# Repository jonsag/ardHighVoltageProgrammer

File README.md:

# ardHighVoltageProgrammer

## Links

[https://mightyohm.com/blog/products/hv-rescue-shield-2-x/](https://mightyohm.com/blog/products/hv-rescue-shield-2-x/)  

[https://www.instructables.com/HV-Rescue-Simple/](https://www.instructables.com/HV-Rescue-Simple/)  
[https://mightyohm.com/blog/2008/09/arduino-based-avr-high-voltage-programmer/](https://mightyohm.com/blog/2008/09/arduino-based-avr-high-voltage-programmer/)  
[https://microtherion.github.io/ScratchMonkey/HVPP.html](https://microtherion.github.io/ScratchMonkey/HVPP.html)  
[https://www.instructables.com/AVR-High-voltage-programming-Fuses-rescue/](https://www.instructables.com/AVR-High-voltage-programming-Fuses-rescue/)  
[http://denki.world3.net/avr_rescue.html](http://denki.world3.net/avr_rescue.html)  

[https://www.gmsystems.com/switching-reg-calculator-for-mc-34063-or-mc33063.html](https://www.gmsystems.com/switching-reg-calculator-for-mc-34063-or-mc33063.html)

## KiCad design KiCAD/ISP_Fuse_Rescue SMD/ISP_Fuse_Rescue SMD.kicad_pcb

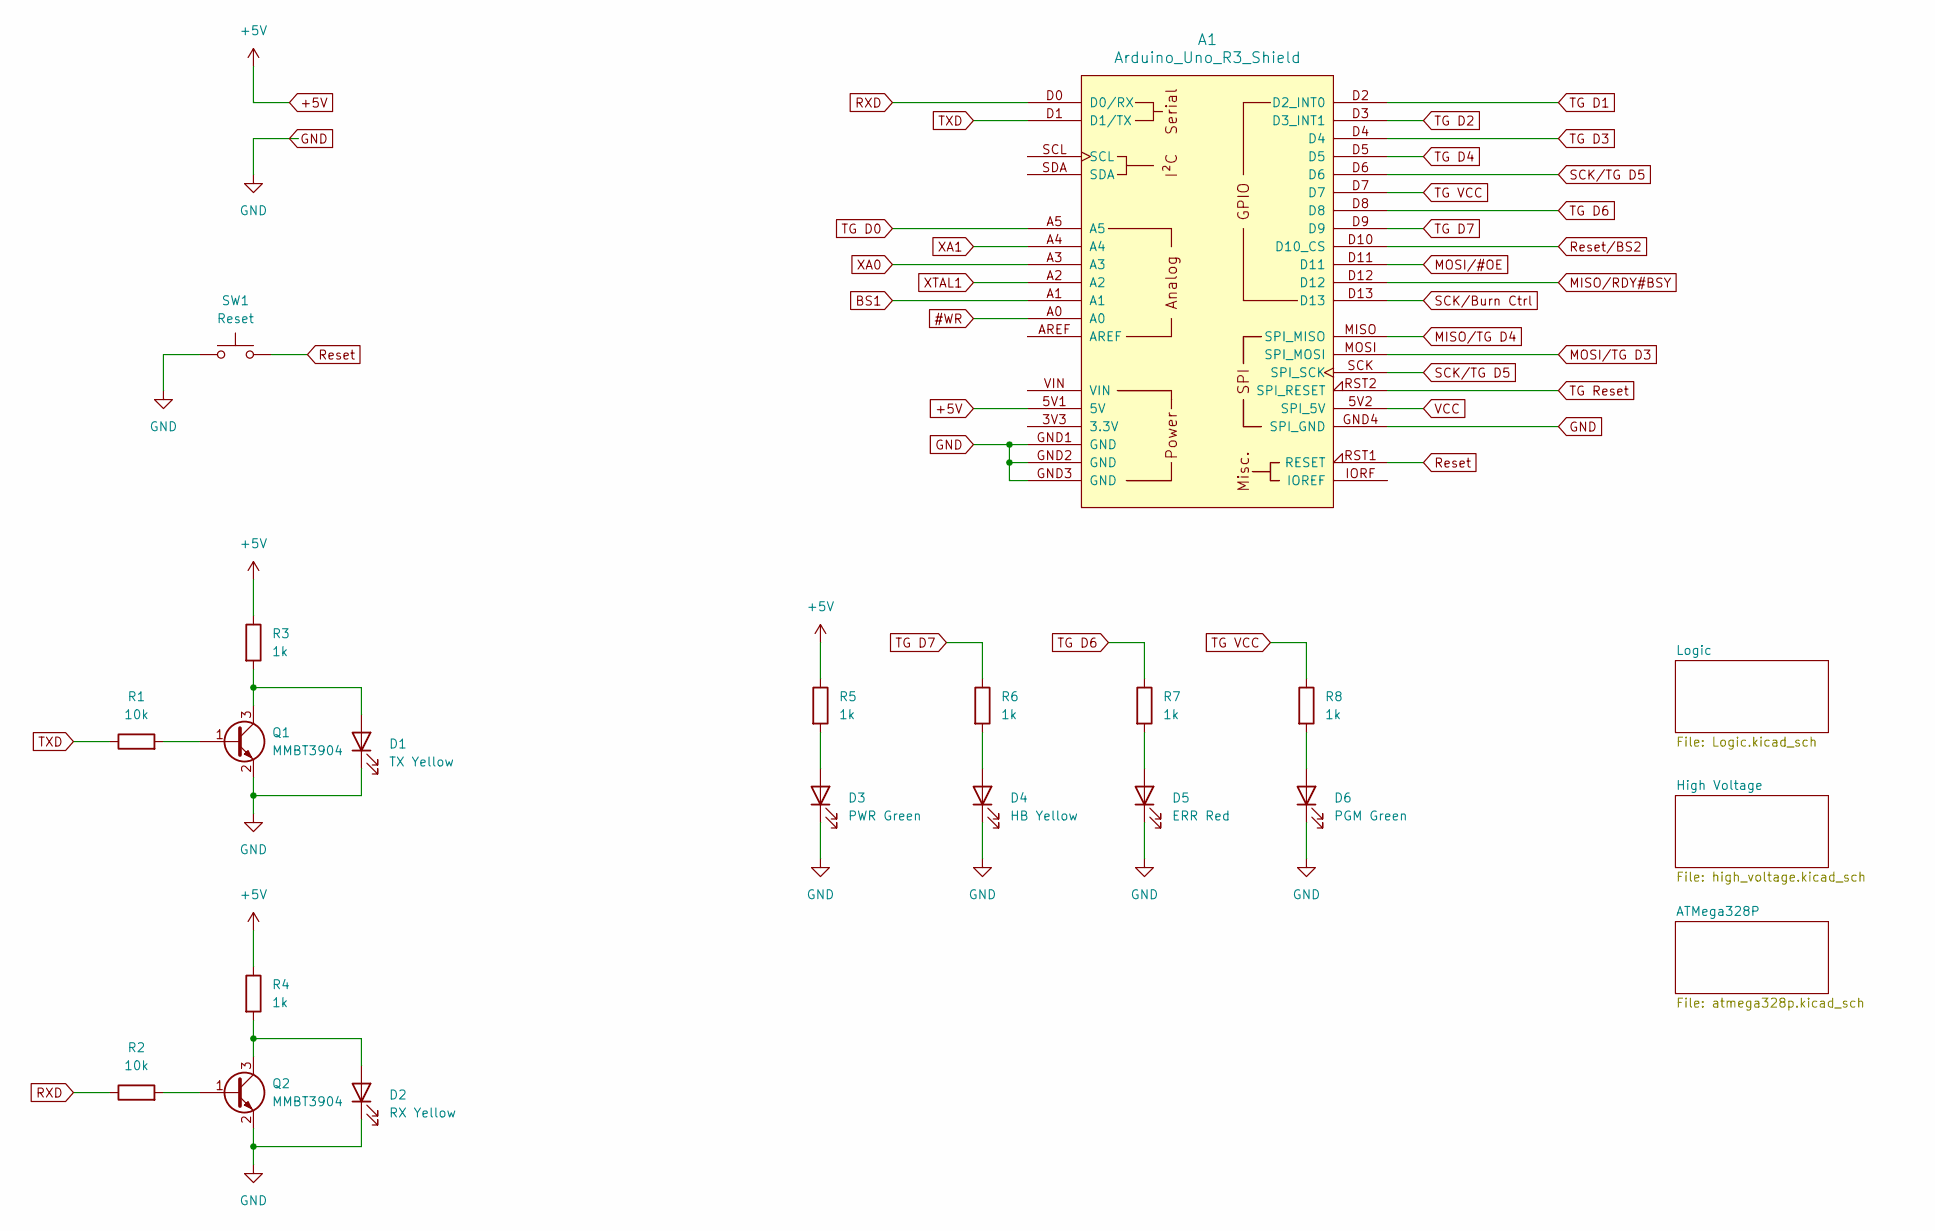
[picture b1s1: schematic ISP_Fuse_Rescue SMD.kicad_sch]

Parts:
A1: Arduino_Uno_R3_Shield; Arduino_UNO_R3_shield_incl ICSP_headers_large
D1: TX Yellow; LED_0805_2012Metric_Pad1.15x1.40mm_HandSolder
D2: RX Yellow; LED_0805_2012Metric_Pad1.15x1.40mm_HandSolder
D3: PWR Green; LED_0805_2012Metric_Pad1.15x1.40mm_HandSolder
D4: HB Yellow; LED_0805_2012Metric_Pad1.15x1.40mm_HandSolder
D5: ERR Red; LED_0805_2012Metric_Pad1.15x1.40mm_HandSolder
D6: PGM Green; LED_0805_2012Metric_Pad1.15x1.40mm_HandSolder
Q1, Q2: MMBT3904; SOT-23_Handsoldering
R1, R2: 10k; R_1206_3216Metric_Pad1.30x1.75mm_HandSolder
R3, R4, R5, R6, R7, R8: 1k; R_1206_3216Metric_Pad1.30x1.75mm_HandSolder
SW1: Reset; Switch tactile Omron B3S SMD

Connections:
#WR: A1.A0; also elsewhere on the board
+5V: A1.5V1 (5V), R3.1, R4.1, R5.1; also elsewhere on the board
BS1: A1.A1; also elsewhere on the board
GND: A1.GND1 (GND), A1.GND2 (GND), A1.GND3 (GND), A1.GND4 (SPI_GND), D1.1 (K), D2.1 (K), D3.1 (K), D4.1 (K), D5.1 (K), D6.1 (K), Q1.2 (E), Q2.2 (E), SW1.1; also elsewhere on the board
MISO/RDY#BSY: A1.D12; also elsewhere on the board
MISO/TG D4: A1.MISO (SPI_MISO); also elsewhere on the board
MOSI/#OE: A1.D11; also elsewhere on the board
MOSI/TG D3: A1.MOSI (SPI_MOSI); also elsewhere on the board
unnamed: D1.2 (A), Q1.3 (C), R3.2
unnamed: D2.2 (A), Q2.3 (C), R4.2
unnamed: D3.2 (A), R5.2
unnamed: D4.2 (A), R6.2
unnamed: D5.2 (A), R7.2
unnamed: D6.2 (A), R8.2
unnamed: Q1.1 (B), R1.2
unnamed: Q2.1 (B), R2.2
RXD: A1.D0 (D0/RX), R2.1
Reset: A1.RST1 (RESET), SW1.2
Reset/BS2: A1.D10 (D10_CS); also elsewhere on the board
SCK/Burn Ctrl: A1.D13; also elsewhere on the board
SCK/TG D5: A1.D6, A1.SCK (SPI_SCK); also elsewhere on the board
TG D0: A1.A5; also elsewhere on the board
TG D1: A1.D2 (D2_INT0); also elsewhere on the board
TG D2: A1.D3 (D3_INT1); also elsewhere on the board
TG D3: A1.D4; also elsewhere on the board
TG D4: A1.D5; also elsewhere on the board
TG D6: A1.D8, R7.1; also elsewhere on the board
TG D7: A1.D9, R6.1; also elsewhere on the board
TG Reset: A1.RST2 (SPI_RESET)
TG VCC: A1.D7, R8.1; also elsewhere on the board
TXD: A1.D1 (D1/TX), R1.1
VCC: A1.5V2 (SPI_5V)
XA1: A1.A4; also elsewhere on the board
XTAL1: A1.A2; also elsewhere on the board

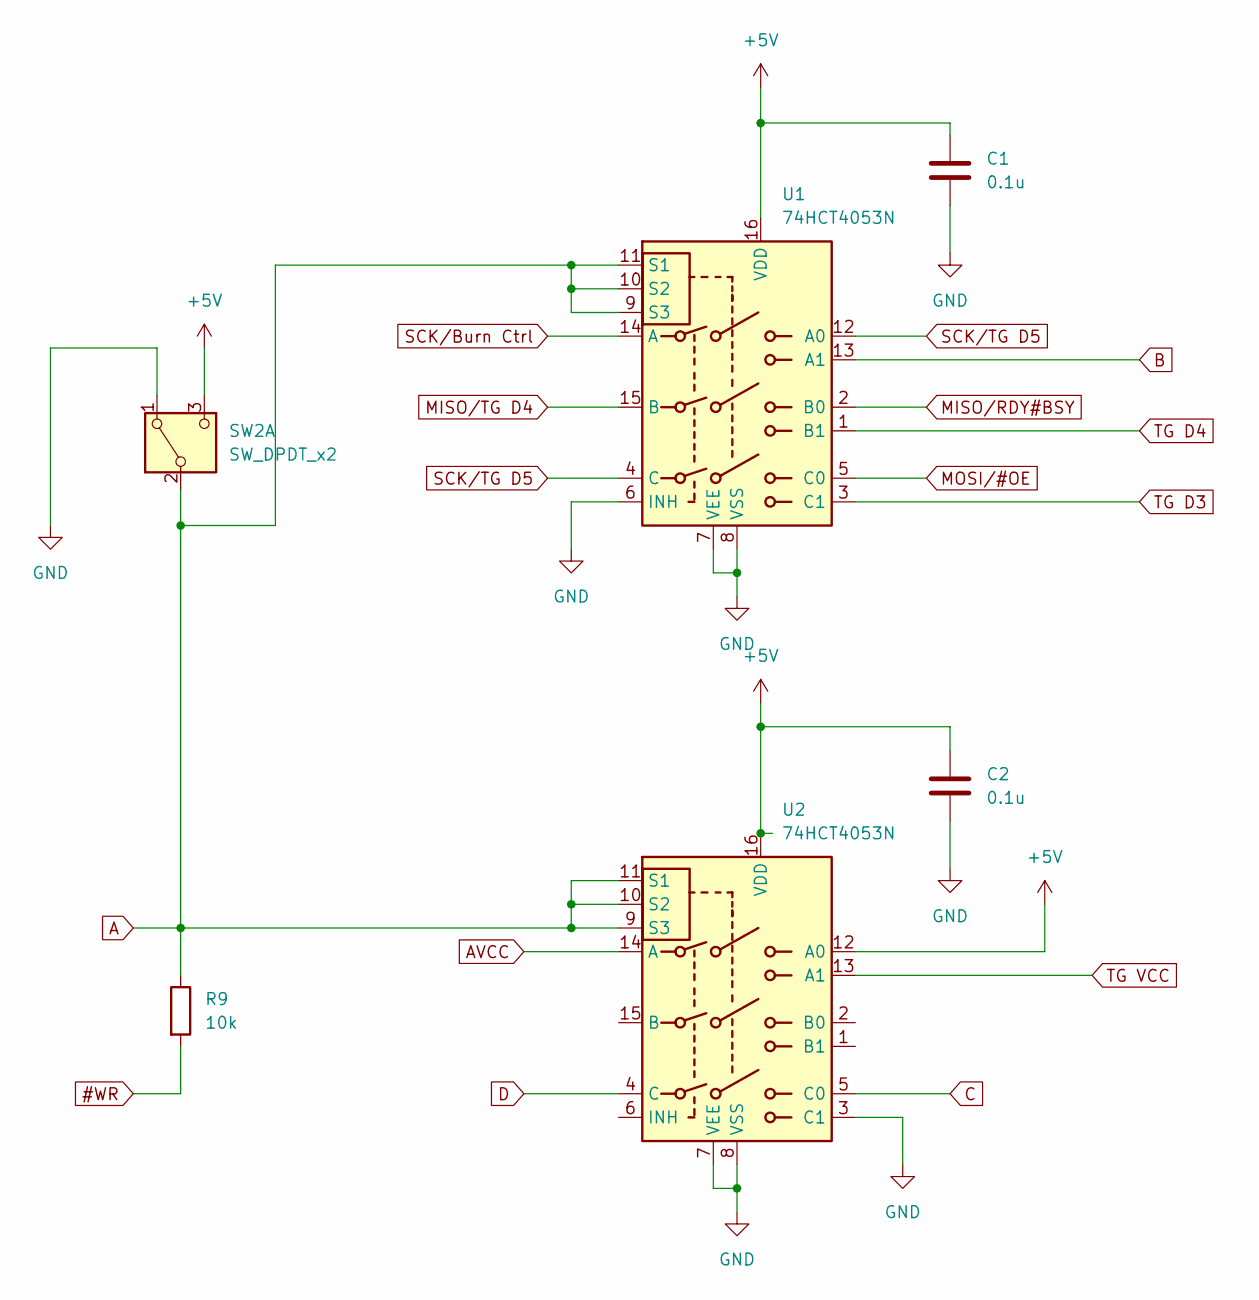
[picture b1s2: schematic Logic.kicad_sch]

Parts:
C1, C2: 0.1u; C_1206_3216Metric_Pad1.33x1.80mm_HandSolder
R9: 10k; R_1206_3216Metric_Pad1.30x1.75mm_HandSolder
SW2: SW_DPDT_x2; Switch slide 2-pole on-on
U1, U2: 74HCT4053N; SOIC-16_3.9x9.9mm_P1.27mm

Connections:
#WR: R9.2; also elsewhere on the board
+5V: C1.1, C2.1, SW2.3 (C), U1.16 (VDD), U2.12 (A0), U2.16 (VDD); also elsewhere on the board
A: R9.1, SW2.2 (B), U1.9 (S3), U1.10 (S2), U1.11 (S1), U2.9 (S3), U2.10 (S2), U2.11 (S1); also elsewhere on the board
AVCC: U2.14 (A); also elsewhere on the board
B: U1.13 (A1); also elsewhere on the board
C: U2.5 (C0); also elsewhere on the board
D: U2.4 (C); also elsewhere on the board
GND: C1.2, C2.2, SW2.1 (A), U1.6 (INH), U1.7 (VEE), U1.8 (VSS), U2.3 (C1), U2.7 (VEE), U2.8 (VSS); also elsewhere on the board
MISO/RDY#BSY: U1.2 (B0); also elsewhere on the board
MISO/TG D4: U1.15 (B); also elsewhere on the board
MOSI/#OE: U1.5 (C0); also elsewhere on the board
SCK/Burn Ctrl: U1.14 (A); also elsewhere on the board
SCK/TG D5: U1.4 (C), U1.12 (A0); also elsewhere on the board
TG D3: U1.3 (C1); also elsewhere on the board
TG D4: U1.1 (B1); also elsewhere on the board
TG VCC: U2.13 (A1); also elsewhere on the board

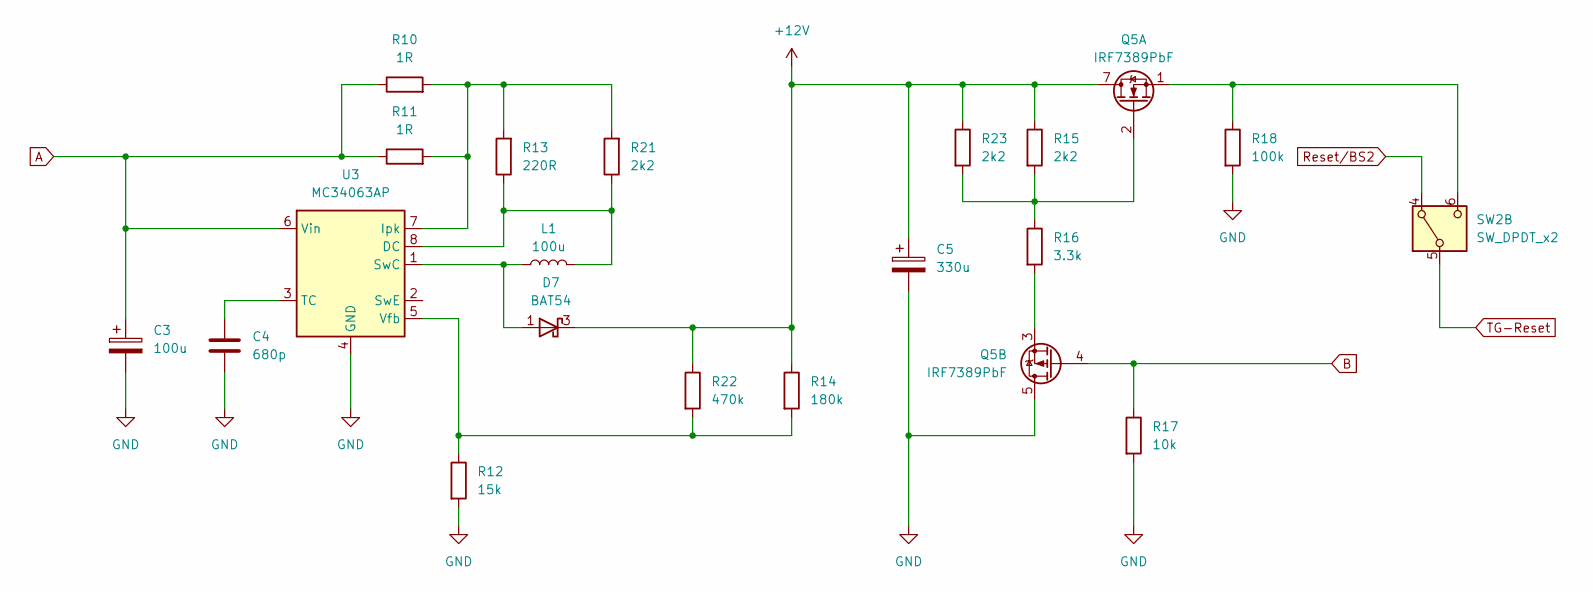
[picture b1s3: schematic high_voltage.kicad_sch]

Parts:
C3: 100u; CP_Elec_8x10
C4: 680p; C_1206_3216Metric_Pad1.33x1.80mm_HandSolder
C5: 330u; CP_Elec_10x10
D7: BAT54; SOT-23_Handsoldering
L1: 100u; L_1210_3225Metric_Pad1.42x2.65mm_HandSolder
Q5: IRF7389PbF; SOIC-8_3.9x4.9mm_P1.27mm
R10, R11: 1R; R_1206_3216Metric_Pad1.30x1.75mm_HandSolder
R12: 15k; R_1206_3216Metric_Pad1.30x1.75mm_HandSolder
R13: 220R; R_1206_3216Metric_Pad1.30x1.75mm_HandSolder
R14: 180k; R_1206_3216Metric_Pad1.30x1.75mm_HandSolder
R15, R21, R23: 2k2; R_1206_3216Metric_Pad1.30x1.75mm_HandSolder
R16: 3.3k; R_1206_3216Metric_Pad1.30x1.75mm_HandSolder
R17: 10k; R_1206_3216Metric_Pad1.30x1.75mm_HandSolder
R18: 100k; R_1206_3216Metric_Pad1.30x1.75mm_HandSolder
R22: 470k; R_1206_3216Metric_Pad1.30x1.75mm_HandSolder
SW2: SW_DPDT_x2; Switch slide 2-pole on-on
U3: MC34063AP; DIP-8_W7.62mm_Socket_w_dip_packet_LongPads

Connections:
+12V: C5.1, D7.3 (K), Q5.7 (D), Q5.8 (D), R14.1, R15.1, R22.1, R23.1
A: C3.1, R10.1, R11.1, U3.6 (Vin); also elsewhere on the board
B: Q5.4 (G), R17.1; also elsewhere on the board
GND: C3.2, C4.2, C5.2, Q5.5 (D), Q5.6 (D), R12.2, R17.2, R18.2, U3.4 (GND); also elsewhere on the board
unnamed: D7.1 (A), L1.1, U3.1 (SwC)
unnamed: Q5.2 (G), R15.2, R16.1, R23.2
unnamed: Q5.1 (S), R18.1, SW2.6 (C)
unnamed: Q5.3 (1), R16.2
unnamed: L1.2, R13.1, R21.1, U3.8 (DC)
unnamed: R10.2, R11.2, R13.2, R21.2, U3.7 (Ipk)
unnamed: C4.1, U3.3 (TC)
unnamed: R12.1, R14.2, R22.2, U3.5 (Vfb)
Reset/BS2: SW2.4 (A); also elsewhere on the board
TG-Reset: SW2.5 (B); also elsewhere on the board

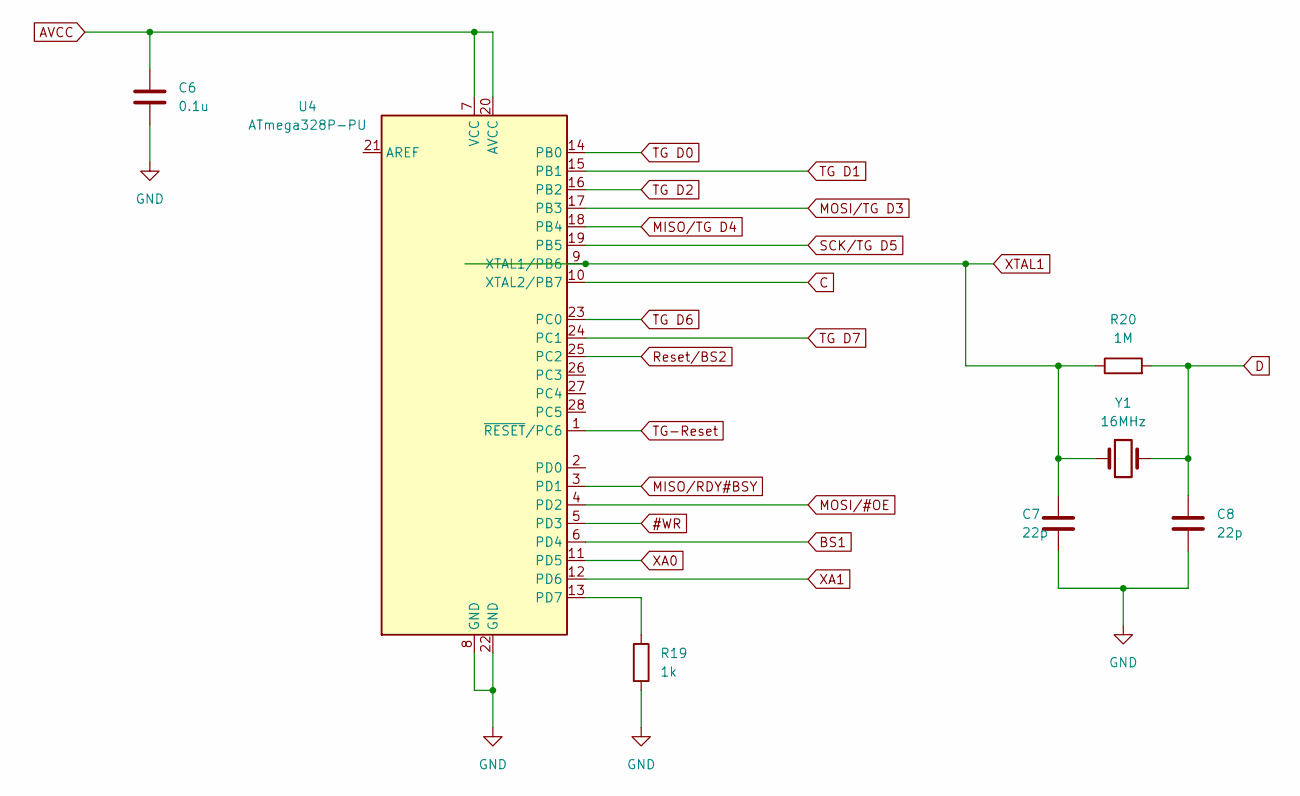
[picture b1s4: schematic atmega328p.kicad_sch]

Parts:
C6: 0.1u; C_1206_3216Metric_Pad1.33x1.80mm_HandSolder
C7, C8: 22p; C_1206_3216Metric_Pad1.33x1.80mm_HandSolder
R19: 1k; R_1206_3216Metric_Pad1.30x1.75mm_HandSolder
R20: 1M; R_1206_3216Metric_Pad1.30x1.75mm_HandSolder
U4: ATmega328P-PU; ZIF_DIP_Socket-28_W6.9_W7.62_W7.62_W12.7_W13.5_large
Y1: 16MHz; Crystal_HC49-4H_Vertical_large

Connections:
#WR: U4.5 (PD3); also elsewhere on the board
AVCC: C6.1, U4.7 (VCC), U4.20 (AVCC); also elsewhere on the board
BS1: U4.6 (PD4); also elsewhere on the board
C: U4.10 (XTAL2/PB7); also elsewhere on the board
D: C8.1, R20.2, Y1.2; also elsewhere on the board
GND: C6.2, C7.2, C8.2, R19.2, U4.8 (GND), U4.22 (GND); also elsewhere on the board
MISO/RDY#BSY: U4.3 (PD1); also elsewhere on the board
MISO/TG D4: U4.18 (PB4); also elsewhere on the board
MOSI/#OE: U4.4 (PD2); also elsewhere on the board
MOSI/TG D3: U4.17 (PB3); also elsewhere on the board
unnamed: R19.1, U4.13 (PD7)
Reset/BS2: U4.25 (PC2); also elsewhere on the board
SCK/TG D5: U4.19 (PB5); also elsewhere on the board
TG D0: U4.14 (PB0); also elsewhere on the board
TG D1: U4.15 (PB1); also elsewhere on the board
TG D2: U4.16 (PB2); also elsewhere on the board
TG D6: U4.23 (PC0); also elsewhere on the board
TG D7: U4.24 (PC1); also elsewhere on the board
TG-Reset: U4.1 (~RESET/PC6); also elsewhere on the board
XA0: U4.11 (PD5)
XA1: U4.12 (PD6); also elsewhere on the board
XTAL1: C7.1, R20.1, U4.9 (XTAL1/PB6), Y1.1; also elsewhere on the board

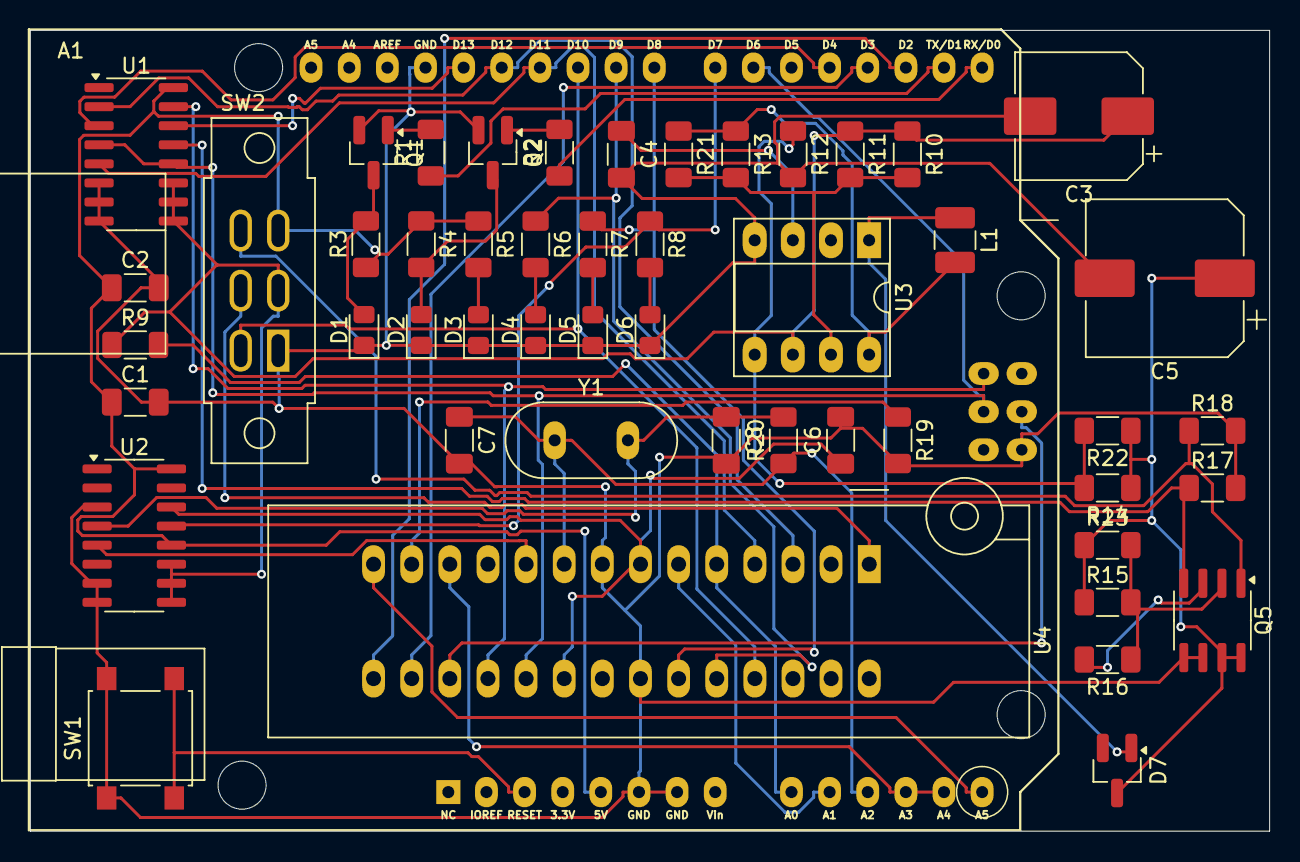
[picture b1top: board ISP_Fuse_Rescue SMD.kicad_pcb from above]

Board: 2 copper layers, 82.6 x 53.3 mm, 50 parts (0 on the bottom side), 48 nets.

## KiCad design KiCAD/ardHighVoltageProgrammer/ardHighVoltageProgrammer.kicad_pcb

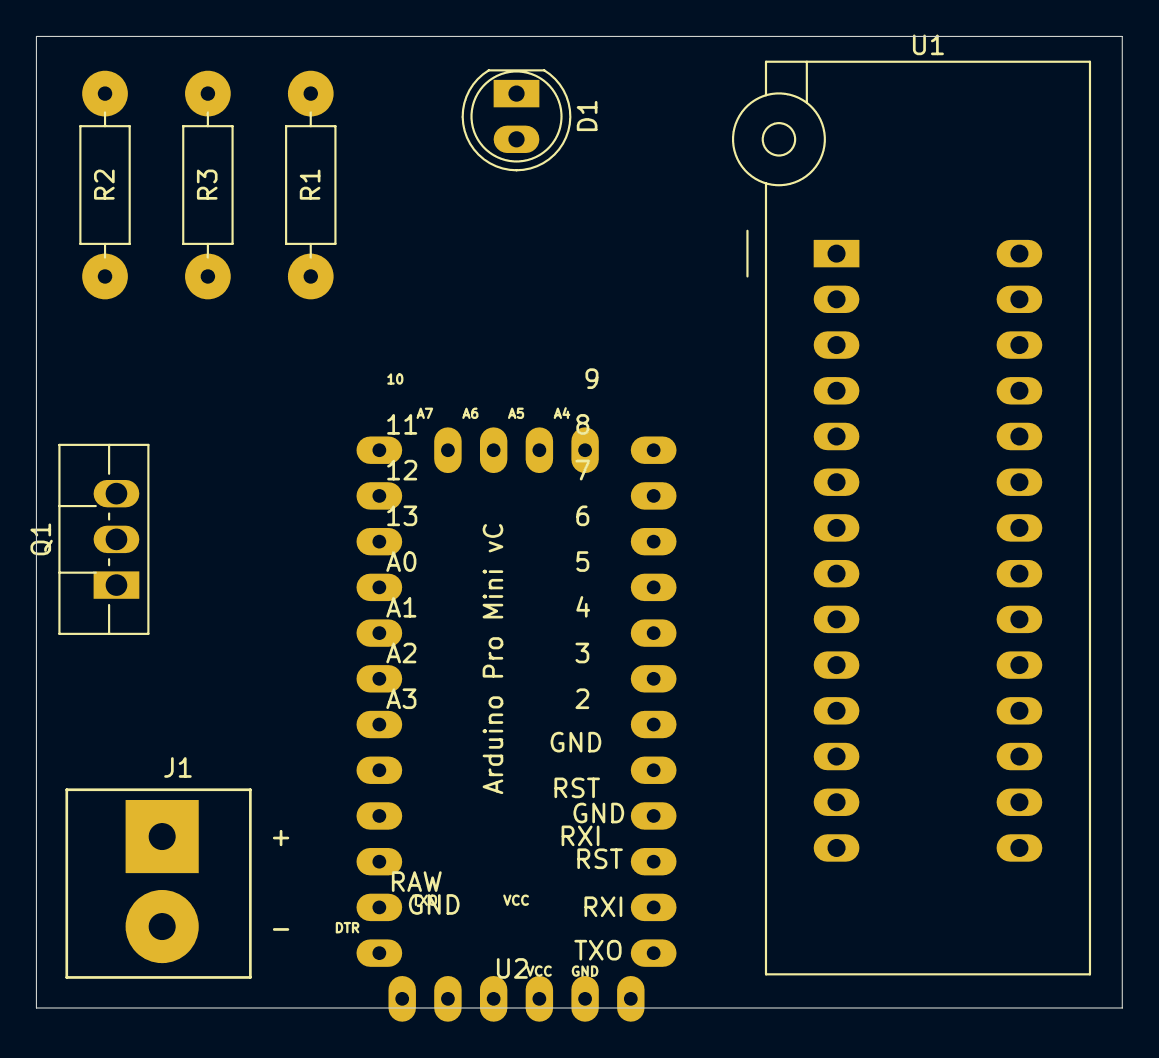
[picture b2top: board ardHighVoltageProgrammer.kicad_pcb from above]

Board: 2 copper layers, 60.3 x 54.0 mm, 8 parts (0 on the bottom side), 24 nets, no tracks yet.

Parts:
D1: LED; LED_D5.0mm_larger_pads
J1: 2-pin_power_input_header; 2-pole_power_in_screw_terminal
Q1: 2N3904; TO-220F-3_Vertical_large
R1: 390R; R_Axial_DIN0207_L6.3mm_D2.5mm_P10.16mm_Horizontal_larger_pa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
R2, R3: 1k; R_Axial_DIN0207_L6.3mm_D2.5mm_P10.16mm_Horizontal_larger_pa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
U1: ATmega328P-PU; ZIF_DIP_Socket-28_W6.9_W7.62_W10.16_W12.7_W13.5_3M_228-4817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
U2: Arduino_Mini_Pro; Arduino_Pro_Mini_vC_larger_pads

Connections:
+5V: D1.2, U1.7, U1.20, U2.16
+12V: J1.1, R2.1
BS1: U1.6, U2.18
BS2: U1.25, U2.12
DATA0: U1.14, U2.19
DATA1: U1.15, U2.1
DATA2: U1.16, U2.5
DATA3: U1.17, U2.6
DATA4: U1.18, U2.7
DATA5: U1.19, U2.8
DATA6: U1.23, U2.9
DATA7: U1.24, U2.10
GND: J1.2, Q1.1, U1.8, U1.22, U2.14
unnamed: D1.1, R1.1
unnamed: Q1.2, R3.2
PAGEL: U1.13, U2.26
RDY: U1.3, U2.21
XA0: U1.11, U2.11
XA1: U1.12, U2.25
XTAL1: U1.9, U2.17
~OE: U1.4, U2.23
~RESET: Q1.3, R2.2, U1.1
~RST: R1.2, R3.1, U2.20
~WR: U1.5, U2.24

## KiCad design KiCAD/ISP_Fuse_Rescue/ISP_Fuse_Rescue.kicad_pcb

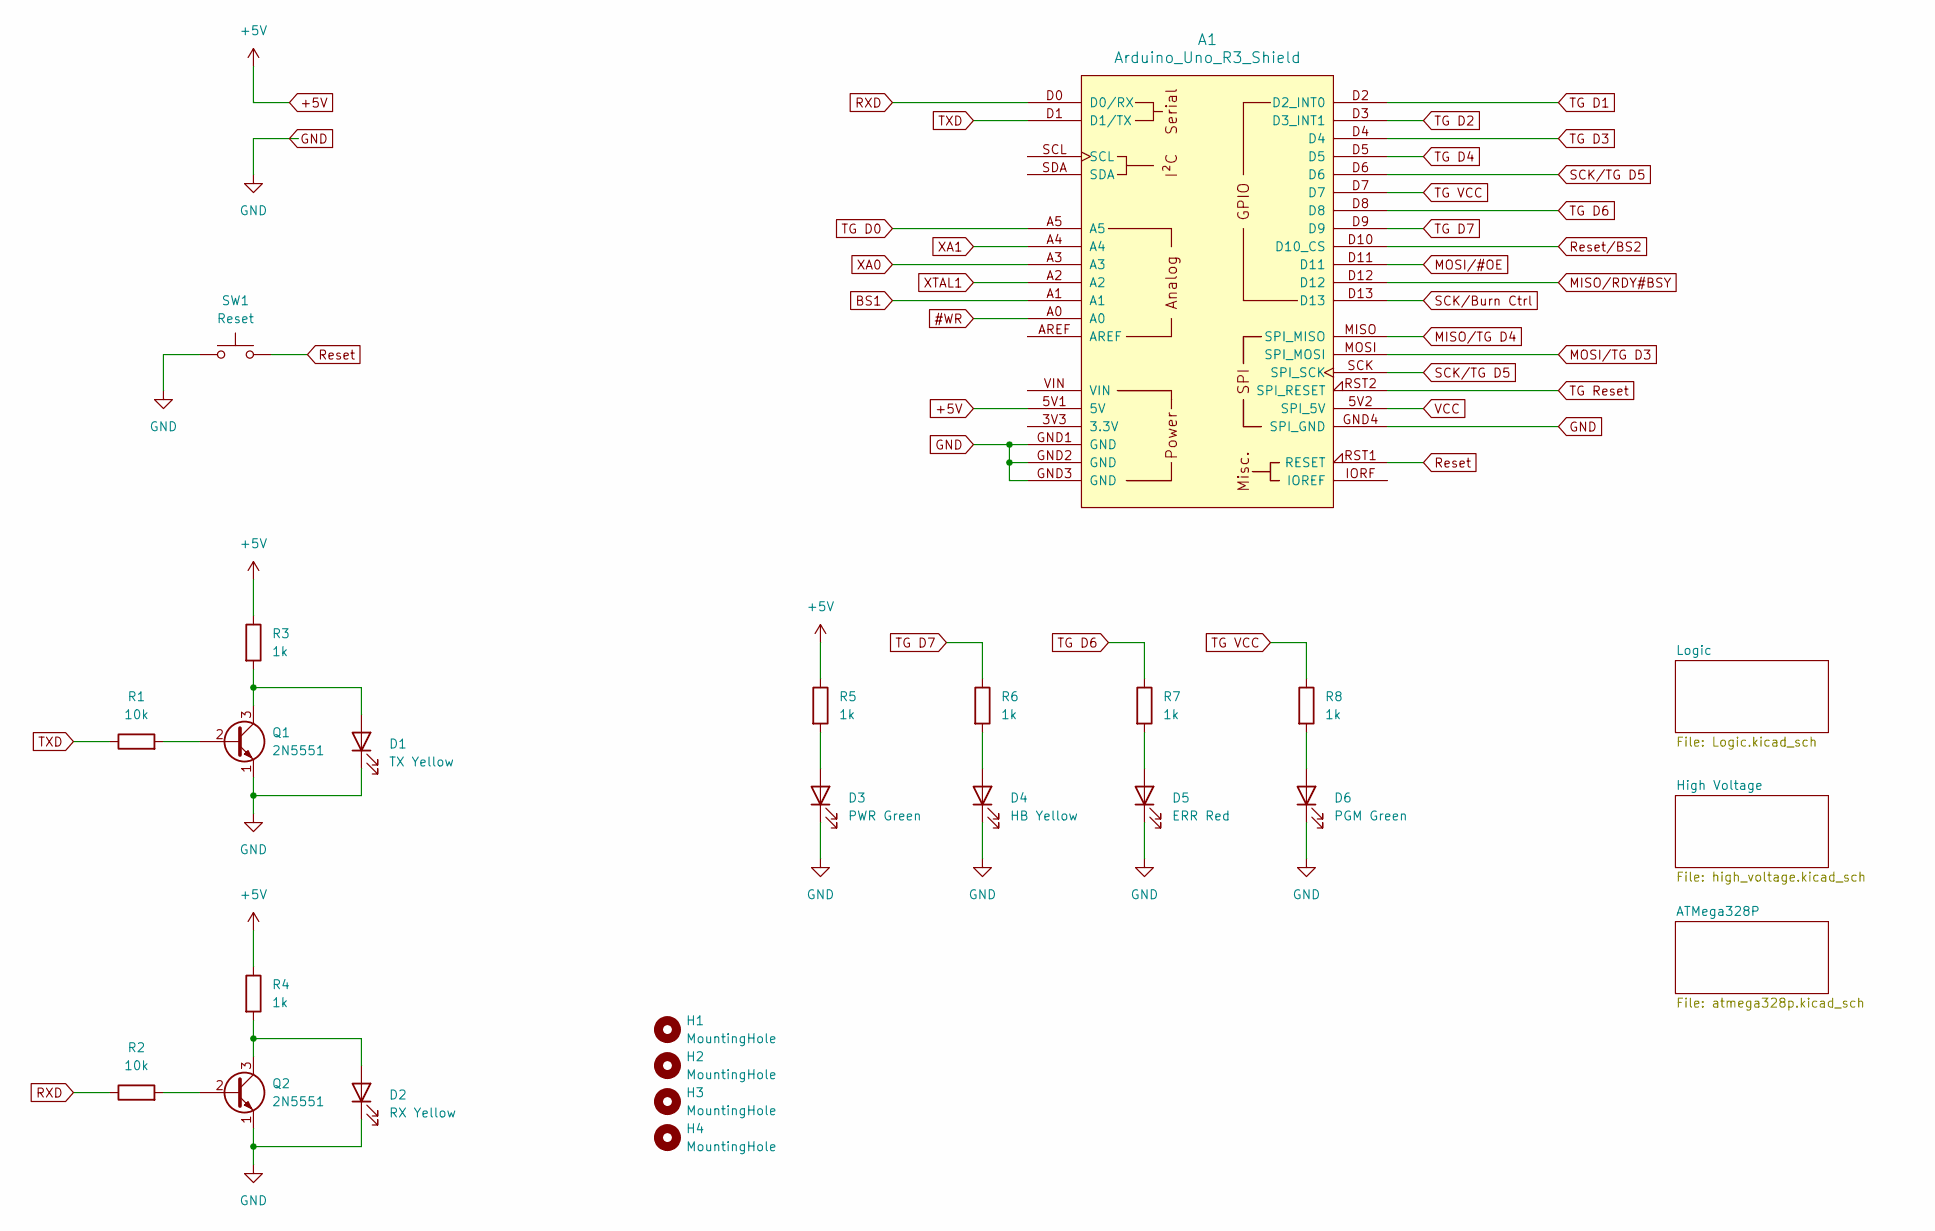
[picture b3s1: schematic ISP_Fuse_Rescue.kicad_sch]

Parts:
A1: Arduino_Uno_R3_Shield; Arduino_UNO_R3_shield_incl ICSP_headers_large
D1: TX Yellow; LED_D5.0mm_large
D2: RX Yellow; LED_D5.0mm_large
D3: PWR Green; LED_D5.0mm_large
D4: HB Yellow; LED_D5.0mm_large
D5: ERR Red; LED_D5.0mm_large
D6: PGM Green; LED_D5.0mm_large
H1, H2, H3, H4: MountingHole; MountingHole_3.2mm_M3
Q1, Q2: 2N5551; TO-92_Inline_Wide_large
R1, R2: 10k; R_Axial_DIN0207_L6.3mm_D2.5mm_P10.16mm_Horizontal_large
R3, R4, R5, R6, R7, R8: 1k; R_Axial_DIN0207_L6.3mm_D2.5mm_P10.16mm_Horizontal_large
SW1: Reset; SW_PUSH_6mm_large

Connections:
#WR: A1.A0; also elsewhere on the board
+5V: A1.5V1 (5V), R3.1, R4.1, R5.1; also elsewhere on the board
BS1: A1.A1; also elsewhere on the board
GND: A1.GND1 (GND), A1.GND2 (GND), A1.GND3 (GND), A1.GND4 (SPI_GND), D1.1 (K), D2.1 (K), D3.1 (K), D4.1 (K), D5.1 (K), D6.1 (K), Q1.1 (E), Q2.1 (E), SW1.1; also elsewhere on the board
MISO/RDY#BSY: A1.D12; also elsewhere on the board
MISO/TG D4: A1.MISO (SPI_MISO); also elsewhere on the board
MOSI/#OE: A1.D11; also elsewhere on the board
MOSI/TG D3: A1.MOSI (SPI_MOSI); also elsewhere on the board
unnamed: D1.2 (A), Q1.3 (C), R3.2
unnamed: D2.2 (A), Q2.3 (C), R4.2
unnamed: D3.2 (A), R5.2
unnamed: D4.2 (A), R6.2
unnamed: D5.2 (A), R7.2
unnamed: D6.2 (A), R8.2
unnamed: Q1.2 (B), R1.2
unnamed: Q2.2 (B), R2.2
RXD: A1.D0 (D0/RX), R2.1
Reset: A1.RST1 (RESET), SW1.2
Reset/BS2: A1.D10 (D10_CS); also elsewhere on the board
SCK/Burn Ctrl: A1.D13; also elsewhere on the board
SCK/TG D5: A1.D6, A1.SCK (SPI_SCK); also elsewhere on the board
TG D0: A1.A5; also elsewhere on the board
TG D1: A1.D2 (D2_INT0); also elsewhere on the board
TG D2: A1.D3 (D3_INT1); also elsewhere on the board
TG D3: A1.D4; also elsewhere on the board
TG D4: A1.D5; also elsewhere on the board
TG D6: A1.D8, R7.1; also elsewhere on the board
TG D7: A1.D9, R6.1; also elsewhere on the board
TG Reset: A1.RST2 (SPI_RESET)
TG VCC: A1.D7, R8.1; also elsewhere on the board
TXD: A1.D1 (D1/TX), R1.1
VCC: A1.5V2 (SPI_5V)
XA1: A1.A4; also elsewhere on the board
XTAL1: A1.A2; also elsewhere on the board

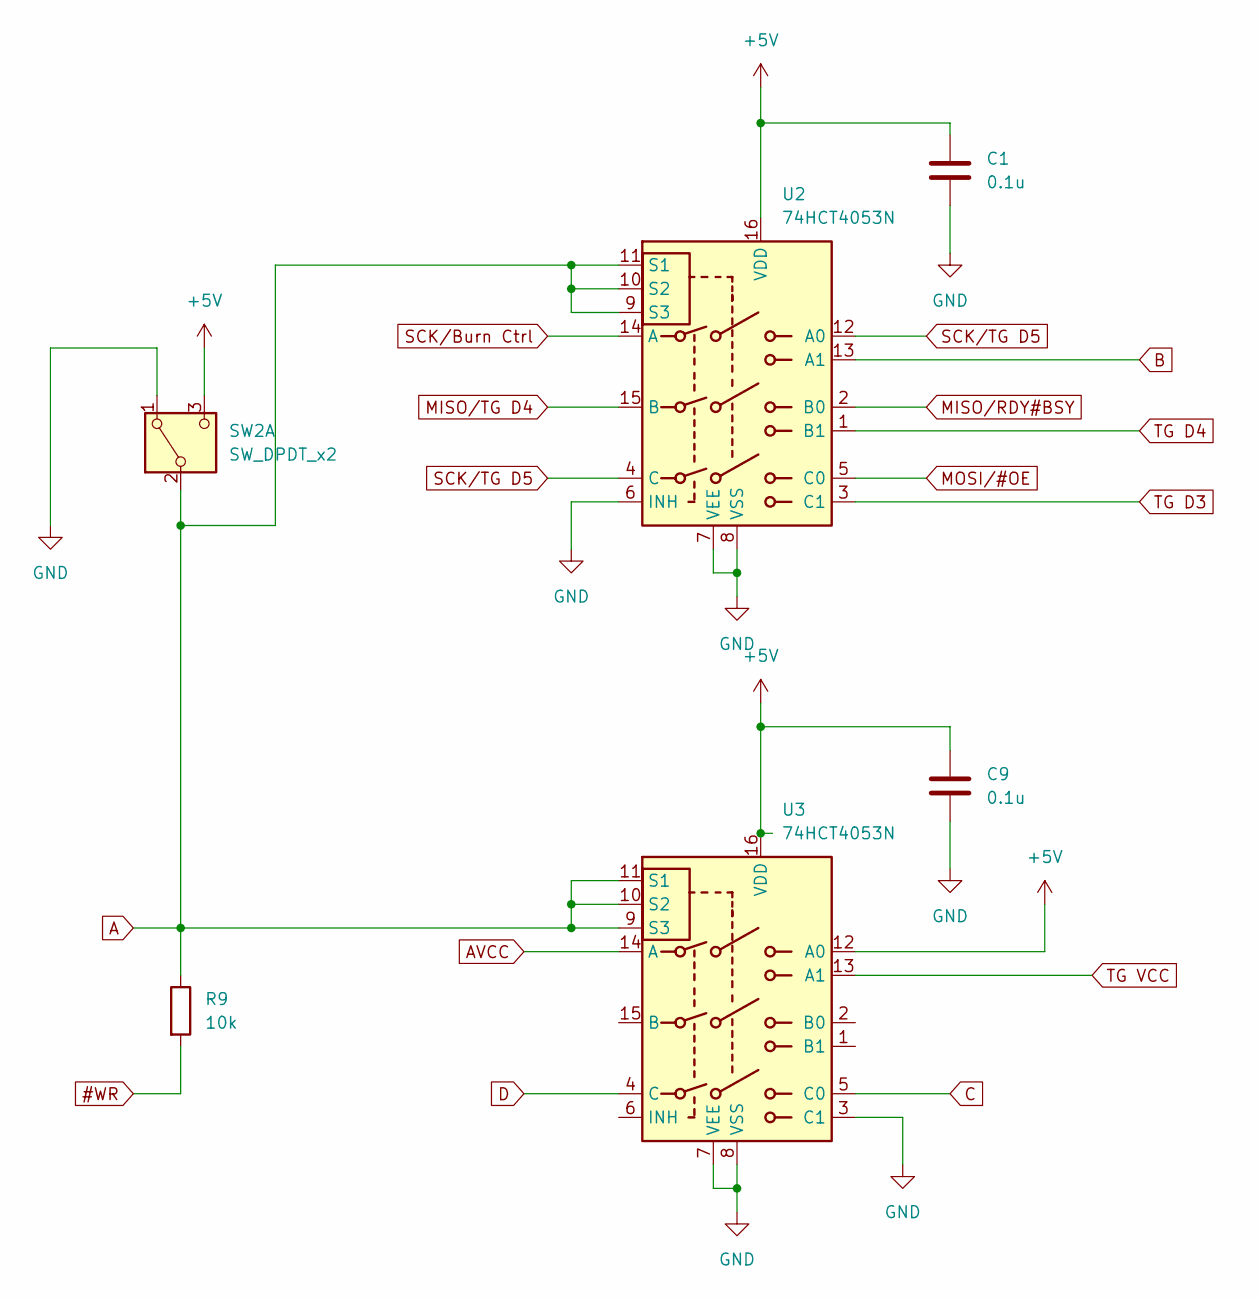
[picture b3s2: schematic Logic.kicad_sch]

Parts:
C1, C9: 0.1u; C_Disc_D3.0mm_W1.6mm_P2.50mm_larg
R9: 10k; R_Axial_DIN0207_L6.3mm_D2.5mm_P10.16mm_Horizontal_large
SW2: SW_DPDT_x2; Switch sub-miniatyr 2-pole on-on
U2, U3: 74HCT4053N; DIP-16_W7.62mm_LongPads w socket

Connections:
#WR: R9.2; also elsewhere on the board
+5V: C1.1, C9.1, SW2.3 (C), U2.16 (VDD), U3.12 (A0), U3.16 (VDD); also elsewhere on the board
A: R9.1, SW2.2 (B), U2.9 (S3), U2.10 (S2), U2.11 (S1), U3.9 (S3), U3.10 (S2), U3.11 (S1); also elsewhere on the board
AVCC: U3.14 (A); also elsewhere on the board
B: U2.13 (A1); also elsewhere on the board
C: U3.5 (C0); also elsewhere on the board
D: U3.4 (C); also elsewhere on the board
GND: C1.2, C9.2, SW2.1 (A), U2.6 (INH), U2.7 (VEE), U2.8 (VSS), U3.3 (C1), U3.7 (VEE), U3.8 (VSS); also elsewhere on the board
MISO/RDY#BSY: U2.2 (B0); also elsewhere on the board
MISO/TG D4: U2.15 (B); also elsewhere on the board
MOSI/#OE: U2.5 (C0); also elsewhere on the board
SCK/Burn Ctrl: U2.14 (A); also elsewhere on the board
SCK/TG D5: U2.4 (C), U2.12 (A0); also elsewhere on the board
TG D3: U2.3 (C1); also elsewhere on the board
TG D4: U2.1 (B1); also elsewhere on the board
TG VCC: U3.13 (A1); also elsewhere on the board

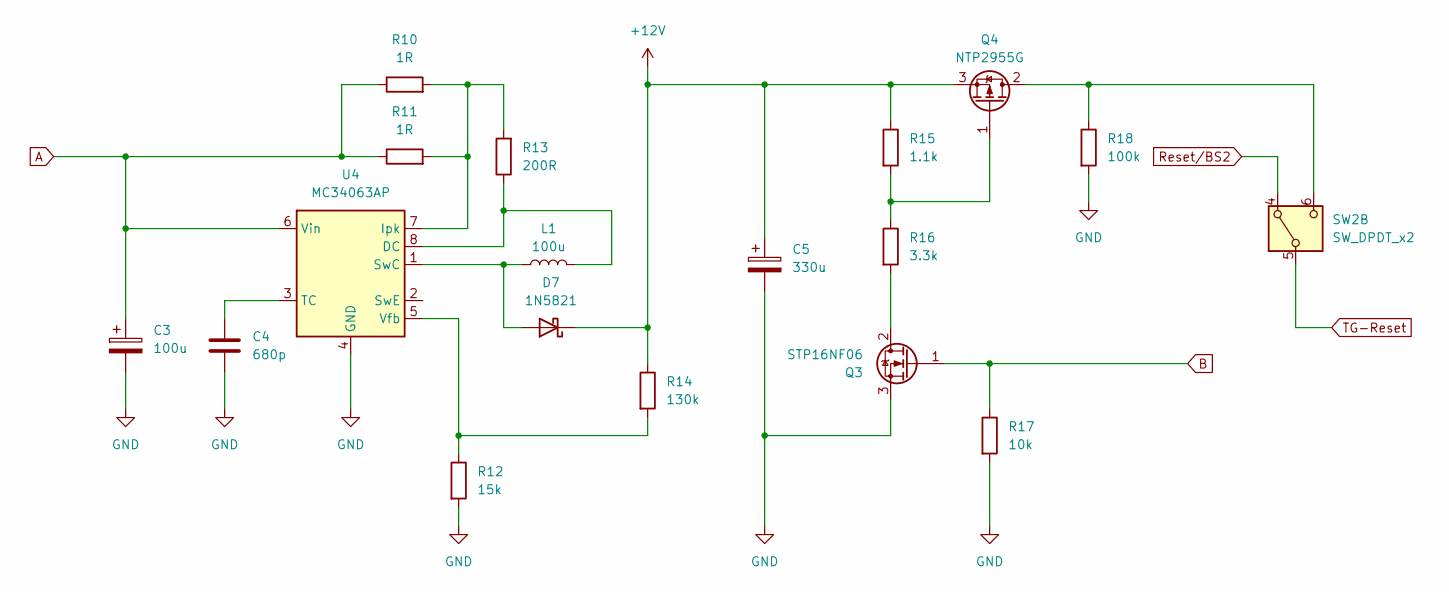
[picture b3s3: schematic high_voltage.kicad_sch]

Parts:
C3: 100u; CP_Radial_D5.0mm_P2.50mm_larger_pads
C4: 680p; C_Disc_D3.0mm_W1.6mm_P2.50mm_larg
C5: 330u; CP_Radial_D5.0mm_P2.50mm_larger_pads
D7: 1N5821; D_DO-201AD_P15.24mm_Horizontal
L1: 100u; L_Radial_D8.7mm_P5.00mm_Fastron_07HCP
Q3: STP16NF06; TO-220-3_Vertical_larger
Q4: NTP2955G; TO-220-3_Vertical_larger
R10, R11: 1R; R_Axial_DIN0207_L6.3mm_D2.5mm_P10.16mm_Horizontal_large
R12: 15k; R_Axial_DIN0207_L6.3mm_D2.5mm_P10.16mm_Horizontal_large
R13: 200R; R_Axial_DIN0207_L6.3mm_D2.5mm_P10.16mm_Horizontal_large
R14: 130k; R_Axial_DIN0207_L6.3mm_D2.5mm_P10.16mm_Horizontal_large
R15: 1.1k; R_Axial_DIN0207_L6.3mm_D2.5mm_P10.16mm_Horizontal_large
R16: 3.3k; R_Axial_DIN0207_L6.3mm_D2.5mm_P10.16mm_Horizontal_large
R17: 10k; R_Axial_DIN0207_L6.3mm_D2.5mm_P10.16mm_Horizontal_large
R18: 100k; R_Axial_DIN0207_L6.3mm_D2.5mm_P10.16mm_Horizontal_large
SW2: SW_DPDT_x2; Switch sub-miniatyr 2-pole on-on
U4: MC34063AP; DIP-8_W7.62mm_Socket_w_dip_packet_LongPads

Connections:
+12V: C5.1, D7.1 (K), Q4.3 (S), R14.1, R15.1
A: C3.1, R10.1, R11.1, U4.6 (Vin); also elsewhere on the board
B: Q3.1 (G), R17.1; also elsewhere on the board
GND: C3.2, C4.2, C5.2, Q3.3 (S), R12.2, R17.2, R18.2, U4.4 (GND); also elsewhere on the board
unnamed: D7.2 (A), L1.1, U4.1 (SwC)
unnamed: Q3.2 (D), R16.2
unnamed: Q4.2 (D), R18.1, SW2.6 (C)
unnamed: Q4.1 (G), R15.2, R16.1
unnamed: L1.2, R13.1, U4.8 (DC)
unnamed: R10.2, R11.2, R13.2, U4.7 (Ipk)
unnamed: C4.1, U4.3 (TC)
unnamed: R12.1, R14.2, U4.5 (Vfb)
Reset/BS2: SW2.4 (A); also elsewhere on the board
TG-Reset: SW2.5 (B); also elsewhere on the board
